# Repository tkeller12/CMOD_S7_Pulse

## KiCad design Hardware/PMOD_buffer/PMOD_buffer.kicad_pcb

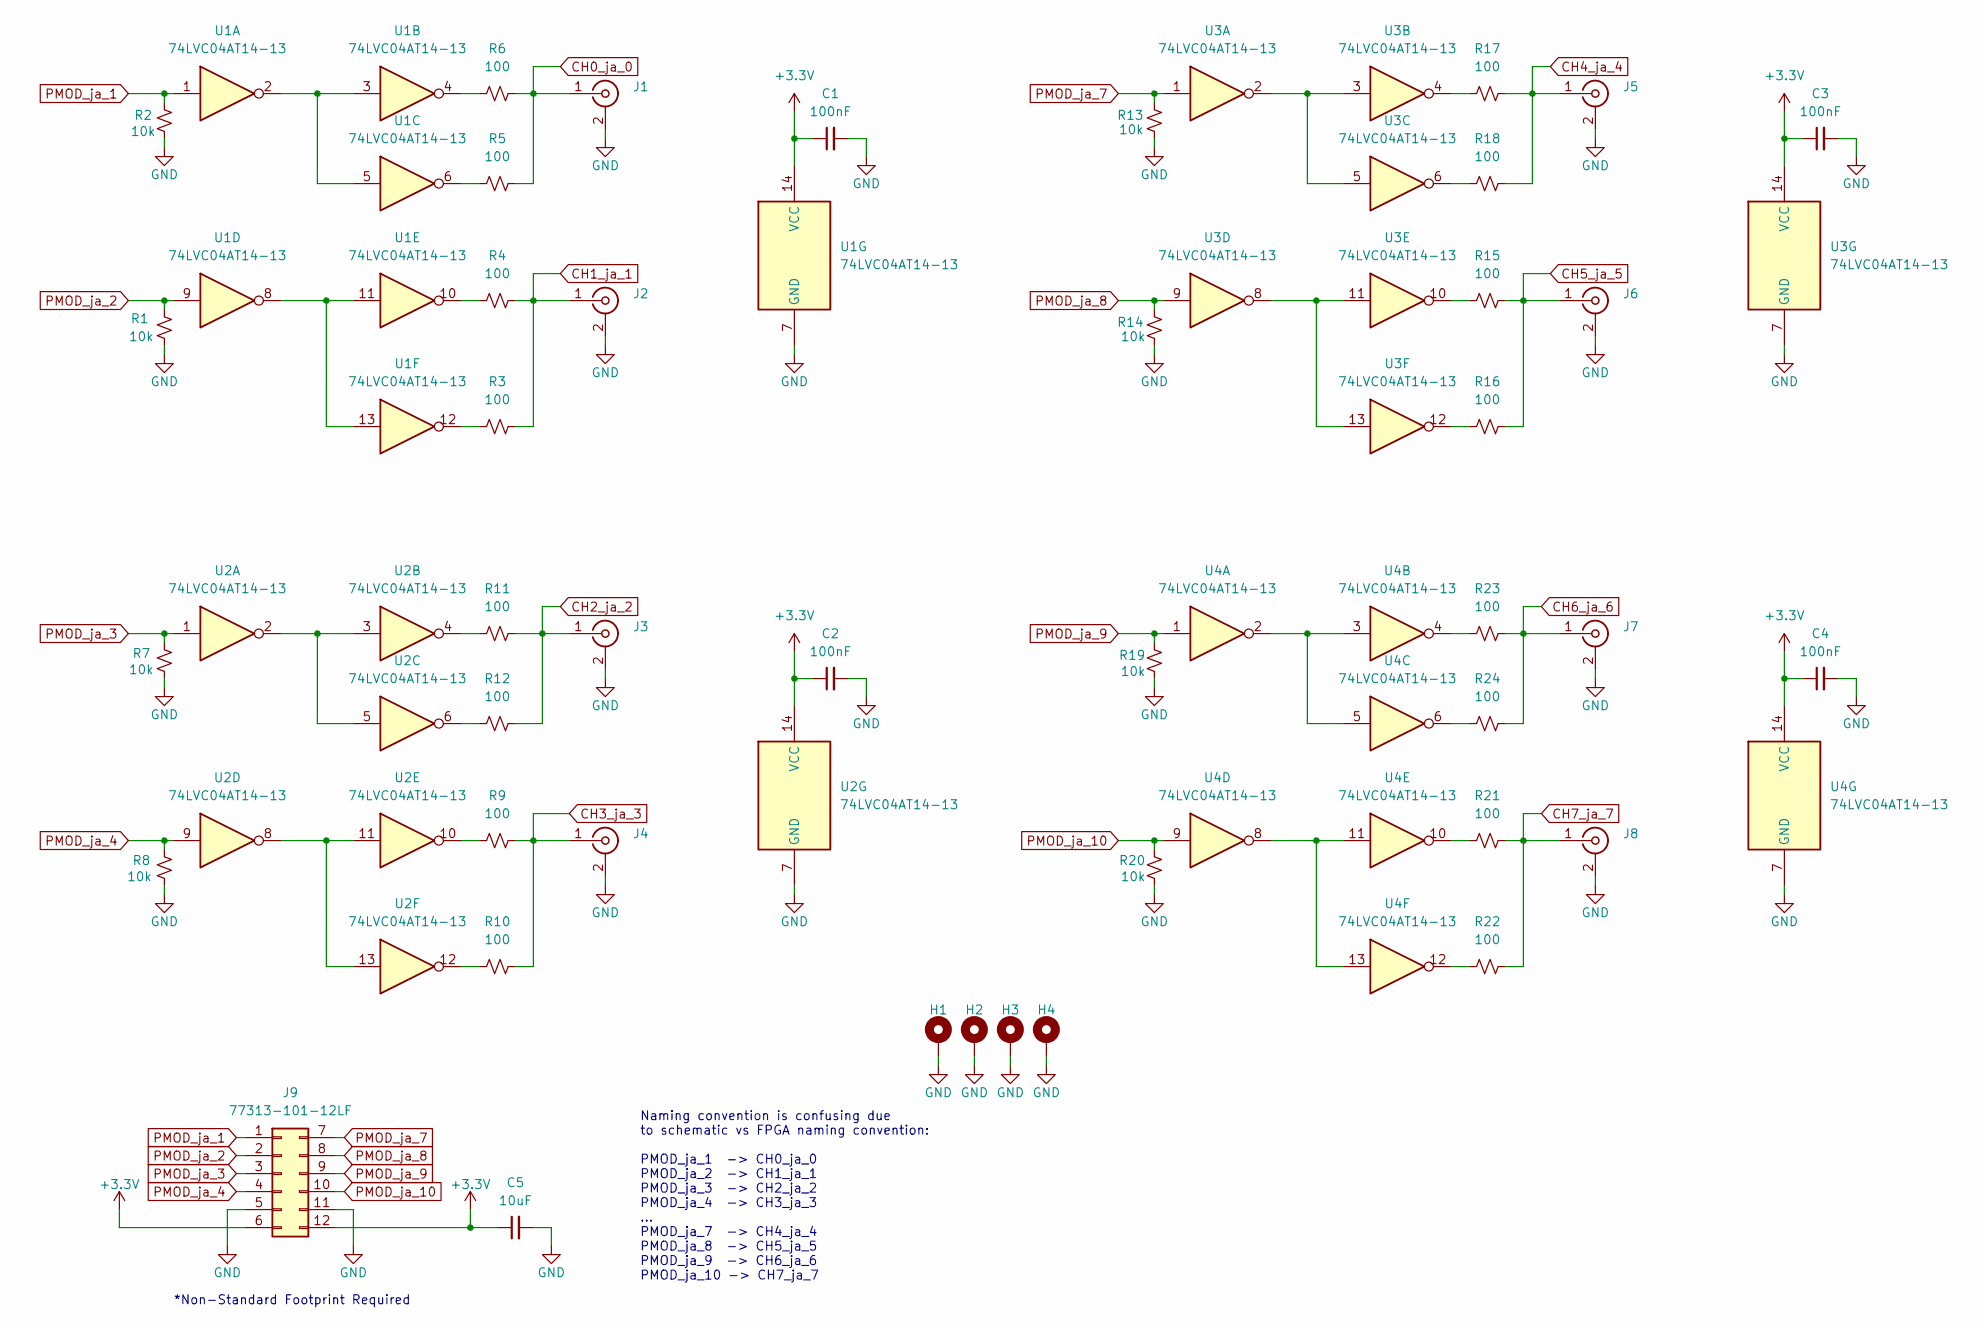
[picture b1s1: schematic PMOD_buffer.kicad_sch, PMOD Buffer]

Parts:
C1, C2, C3, C4: 100nF; C_0805_2012Metric; MPN KGM21NR71H104KT; Digikey 478-KGM21NR71H104KTCT-ND
C5: 10uF; C_0805_2012Metric; MPN CL21A106KOQNNNG; Digikey 1276-6455-1-ND
H1, H2, H3, H4: MountingHole_Pad; 4-40_Hole_Pad
J1, J2, J3, J4, J5, J6, J7, J8: RF2-152-T-00-50-G-HDW; SMA_Amphenol_132291_Vertical; MPN RF2-152-T-00-50-G-HDW; Digikey 2057-RF2-152-T-00-50-G-HDW-ND
J9: 77313-101-12LF; PMOD_PinHeader_2x06_P2.54mm_Vertical; MPN 77313-101-12LF; Digikey 609-5695-ND
R1, R2, R7, R8, R13, R14, R19, R20: 10k; R_0805_2012Metric; MPN CRCW080510K0FKEAC; Digikey 541-3976-1-ND
R3, R4, R5, R6, R9, R10, R11, R12, R15, R16, R17, R18, R21, R22, R23, R24: 100; R_0805_2012Metric; MPN RMCF0805FT100R; Digikey RMCF0805FT100RCT-ND
U1, U2, U3, U4: 74LVC04AT14-13; TSSOP-14_4.4x5mm_P0.65mm; MPN 74LVC04AT14-13; Digikey 31-74LVC04AT14-13CT-ND

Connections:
+3.3V: C1.1, C2.1, C3.1, C4.1, C5.1, J9.6, J9.12, U1.14 (VCC), U2.14 (VCC), U3.14 (VCC), U4.14 (VCC)
CH0_ja_0: J1.1 (In), R5.2, R6.2
CH1_ja_1: J2.1 (In), R3.2, R4.2
CH2_ja_2: J3.1 (In), R11.2, R12.2
CH3_ja_3: J4.1 (In), R9.2, R10.2
CH4_ja_4: J5.1 (In), R17.2, R18.2
CH5_ja_5: J6.1 (In), R15.2, R16.2
CH6_ja_6: J7.1 (In), R23.2, R24.2
CH7_ja_7: J8.1 (In), R21.2, R22.2
GND: C1.2, C2.2, C3.2, C4.2, C5.2, H1.1, H2.1, H3.1, H4.1, J1.2 (Ext), J2.2 (Ext), J3.2 (Ext), J4.2 (Ext), J5.2 (Ext), J6.2 (Ext), J7.2 (Ext), J8.2 (Ext), J9.5, J9.11, R1.2, R2.2, R7.2, R8.2, R13.2, R14.2, R19.2, R20.2, U1.7 (GND), U2.7 (GND), U3.7 (GND), U4.7 (GND)
unnamed: R3.1, U1.12
unnamed: R4.1, U1.10
unnamed: R5.1, U1.6
unnamed: R6.1, U1.4
unnamed: R9.1, U2.10
unnamed: R10.1, U2.12
unnamed: R11.1, U2.4
unnamed: R12.1, U2.6
unnamed: R15.1, U3.10
unnamed: R16.1, U3.12
unnamed: R17.1, U3.4
unnamed: R18.1, U3.6
unnamed: R21.1, U4.10
unnamed: R22.1, U4.12
unnamed: R23.1, U4.4
unnamed: R24.1, U4.6
unnamed: U1.2, U1.3, U1.5
unnamed: U1.8, U1.11, U1.13
unnamed: U2.2, U2.3, U2.5
unnamed: U2.8, U2.11, U2.13
unnamed: U3.2, U3.3, U3.5
unnamed: U3.8, U3.11, U3.13
unnamed: U4.2, U4.3, U4.5
unnamed: U4.8, U4.11, U4.13
PMOD_ja_1: J9.1, R2.1, U1.1
PMOD_ja_2: J9.2, R1.1, U1.9
PMOD_ja_3: J9.3, R7.1, U2.1
PMOD_ja_4: J9.4, R8.1, U2.9
PMOD_ja_7: J9.7, R13.1, U3.1
PMOD_ja_8: J9.8, R14.1, U3.9
PMOD_ja_9: J9.9, R19.1, U4.1
PMOD_ja_10: J9.10, R20.1, U4.9

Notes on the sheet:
*Non-Standard Footprint Required
Naming convention is confusing due to schematic vs FPGA naming convention: PMOD_ja_1 -> CH0_ja_0 PMOD_ja_2 -> CH1_ja_1 PMOD_ja_3 -> CH2_ja_2 PMOD_ja_4 -> CH3_ja_3 ... PMOD_ja_7 -> CH4_ja_4 PMOD_ja_8 -> CH5_ja_5 PMOD_ja_9 -> CH6_ja_6 PMOD_ja_10 -> CH7_ja_7

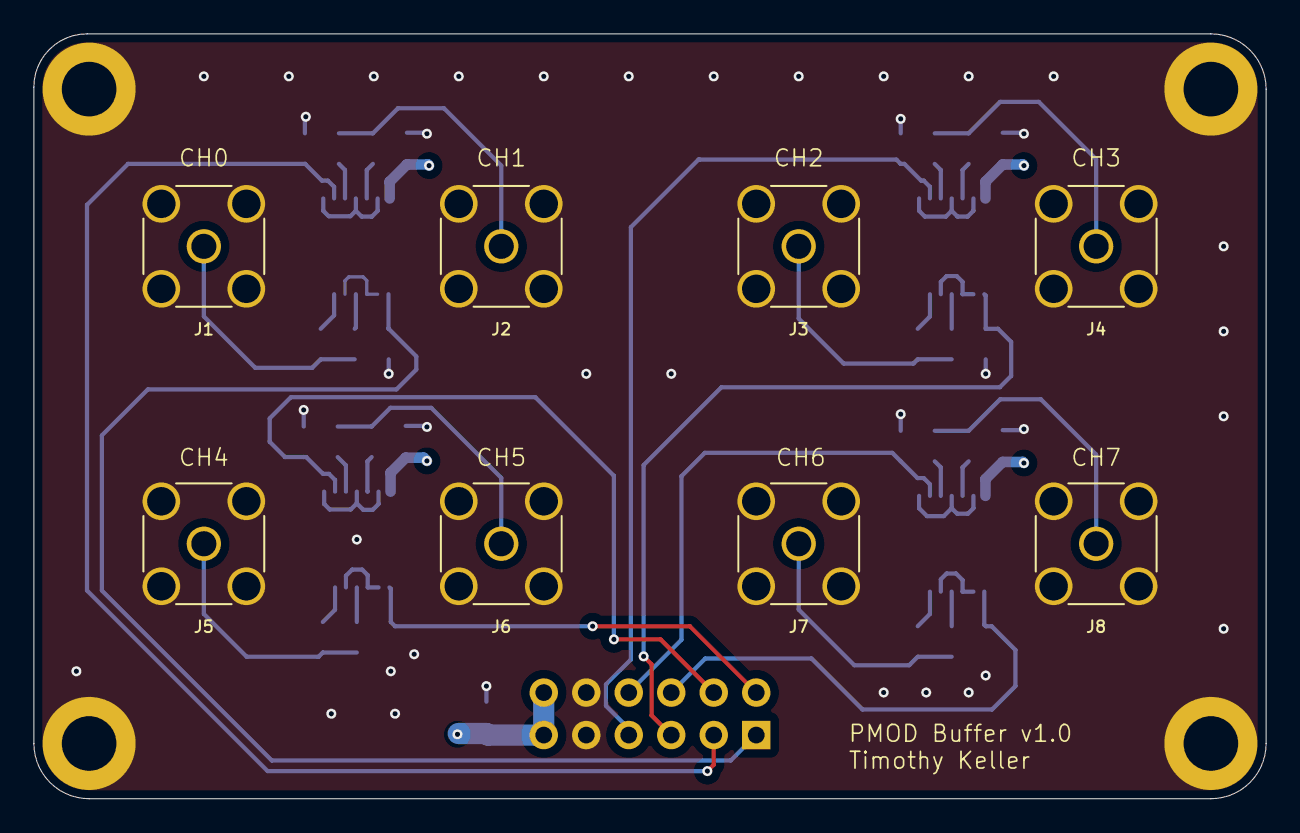
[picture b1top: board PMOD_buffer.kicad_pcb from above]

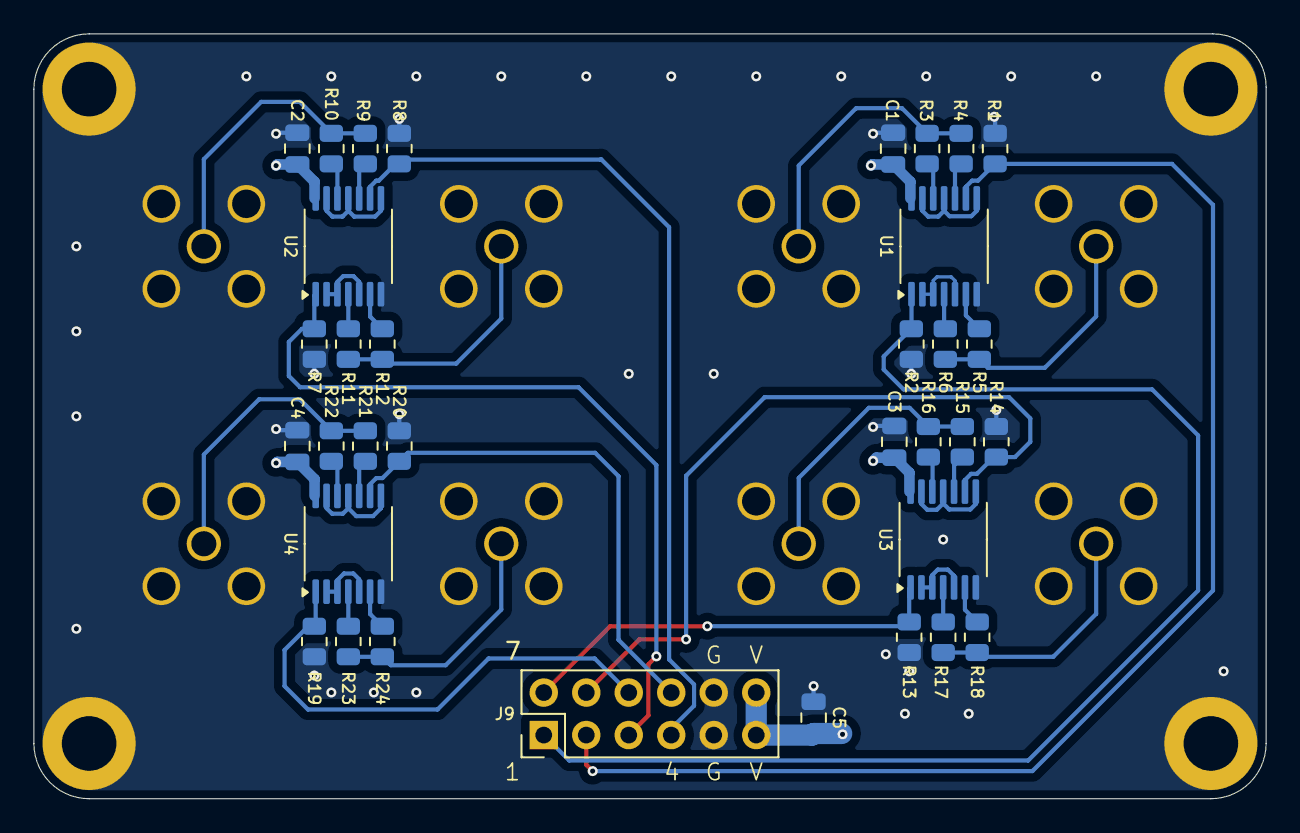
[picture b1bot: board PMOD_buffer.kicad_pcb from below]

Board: 4 copper layers, 73.7 x 45.7 mm, 46 parts (34 on the bottom side), 42 nets.

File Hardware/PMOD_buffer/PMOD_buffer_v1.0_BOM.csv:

"Reference","Value","Datasheet","Footprint","Qty","DNP","Digikey","MPN","Manufacturer","Description"
"C1,C2,C3,C4","100nF","~","Capacitor_SMD:C_0805_2012Metric","4","","478-KGM21NR71H104KTCT-ND","KGM21NR71H104KT","KYOCERA AVX","CAP CER 0.1UF 50V X7R 0805"
"C5","10uF","~","Capacitor_SMD:C_0805_2012Metric","1","","1276-6455-1-ND","CL21A106KOQNNNG","Samsung Electro-Mechanics","CAP CER 10UF 16V X5R 0805"
"J1,J2,J3,J4,J5,J6,J7,J8","RF2-152-T-00-50-G-HDW","RF2-152-T-00-50-G-HDW","Connector_Coaxial:SMA_Amphenol_132291_Vertical","8","","2057-RF2-152-T-00-50-G-HDW-ND","RF2-152-T-00-50-G-HDW","Adam Tech","SMA JACK STR PCB 50OHM 18GHZ BRS"
"J9","77313-101-12LF","~","_tim-Headers:PMOD_PinHeader_2x06_P2.54mm_Vertical","1","","609-5695-ND","77313-101-12LF","Amphenol ICC (FCI)","CONN HEADER VERT 12POS 2.54MM"
"R1,R2,R7,R8,R13,R14,R19,R20","10k","~","Resistor_SMD:R_0805_2012Metric","8","","541-3976-1-ND","CRCW080510K0FKEAC","Vishay Dale","RES 10K OHM 1% 1/8W 0805"
"R3,R4,R5,R6,R9,R10,R11,R12,R15,R16,R17,R18,R21,R22,R23,R24","100","~","Resistor_SMD:R_0805_2012Metric","16","","RMCF0805FT100RCT-ND","RMCF0805FT100R","Stackpole Electronics Inc","RES 100 OHM 1% 1/8W 0805"
"U1,U2,U3,U4","74LVC04AT14-13","http://www.ti.com/lit/gpn/sn74LS04","Package_SO:TSSOP-14_4.4x5mm_P0.65mm","4","","31-74LVC04AT14-13CT-ND","74LVC04AT14-13","Diodes Incorporated","IC INVERTER 6CH 6-INP 14TSSOP"

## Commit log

2024-11-26 Creating Vivado project
2024-11-26 Creating Schematic
2024-11-27 Routing Board
2024-11-28 Adding clocks
2024-12-03 Testing Shift Register
2024-12-04 Removing unnecessary modules
2024-12-04 backups
2024-12-14 Adding vivado project
2024-12-14 WIP Updating pulse programmer verilog code
2024-12-14 Testing pulse programmer core
2024-12-15 Updating pulse programmer core test
2024-12-15 Updating pulse programmer core
2024-12-15 Updating pulse programmer verilog code
2024-12-15 Pulse Programmer working
    WIP addr 0 does not work properly
2024-12-15 Updating python script for writing to pulse programmer
2024-12-15 minor change to python script
2024-12-16 testing dds core
2024-12-16 Minor changes
2024-12-18 Adding gitignore for vim files
2024-12-18 Adding simple blink example
2024-12-18 Using Standard 2-port RAM and assign statements
2024-12-19 Updating RAM
2024-12-19 Implemented wait op code
2024-12-19 Adding GOTO op code
2024-12-20 Implementing Long delay op code
2024-12-23 Adding memory config
2024-12-24 Adding start and stop commands
2024-12-27 Adding simulation to test
2024-12-27 Updating Clocking wizard
2024-12-30 Changing back to 250 MHz clock
2025-07-06 Updating PMOD Buffer BOM
2025-07-07 adding BOM for buffer board
2025-07-07 Generating Gerbers for Buffer
2025-07-11 Adding fab and assem files
2025-07-18 Adding python scripts to generate pulse sequence
2025-07-18 Adding new pulse generator script
2025-07-19 Updates to pulse train script
2025-07-19 Working example for pulse programming sequence
2025-07-19 implementation runs, but can't upload to board
2025-07-19 Fixing issue with severe clock violations, now using 125 MHz clock
2025-07-19 Fixing fpga configuration, new memory file
2025-07-19 Moving examples to new directory
2025-07-19 Creating new python package for pulse programmer
2025-07-19 Updating python package, adding config support
2025-07-19 Created working example
2025-07-19 Cleaning up code
2025-07-19 Adding plot module
2025-07-19 Updating plot function
2025-07-20 Autodetecting serial port
2025-07-20 Fixing issue with plot, adding new troubleshooting script
2025-07-20 Updating documentation with photos
2025-07-20 Cleaning up example script
2026-03-14 Changing clock frequency back to 250 MHz
2026-03-14 Updating documentation for pulse programmer op codes
2026-03-14 updating python scripts for testing, changing resolution to 4ns
2026-03-14 Updating Verilog for 250 MHz clock, fixed bug with address 0
2026-03-14 Adding JUMP op code to pulse programmer
2026-03-15 Adding external clock wizard
2026-03-15 Changing clock to 125 MHz
2026-03-15 Updating documentation, adding table for instructions
2026-03-15 Working on fixing bug with jump
2026-03-16 creating test bench for top module
2026-03-16 Troubleshooting issue with BRAM latency
2026-03-17 Updating pulse programmer core to remove address increment bug
2026-03-17 Adding new memory configuration
2026-03-17 minor change. Added reset for clock
2026-03-17 Auto stash before merge of "develop" and "feature-EXT_10MHz_CLK"
2026-03-17 Updating FPGA frequency to 250 MHz
2026-03-18 Updating documentation
2026-03-21 testing clock frequencies
2026-03-21 Adding lexer
2026-03-21 Starting parser
2026-03-21 Updates to lexer and parser
2026-03-22 Starting to implement AST
2026-03-22 Adding Pulse programmer documentation, support for comments
2026-03-23 Working on edges to states function
2026-03-23 Adding generate_instructions function
2026-03-23 fixing minor bug
2026-03-23 adding plot for states
2026-03-23 Changing config format
2026-03-23 Fixing connectivity bug and cleaning up code
2026-03-23 Moving inverting bits to states
2026-03-24 Adding checks for duty cycle limit and max pulse length limit
2026-03-24 Fixing issue with remove_redundant_edges function
2026-03-24 Adding function to write instructions to file
2026-03-25 Adding new simulation with memory load from file
2026-03-25 Fixing glitch with output during JUMP instruction
2026-03-25 removing comment
2026-03-25 Adding HALT Command
2026-03-26 wip testing LOOP_START and LOOP_STOP
2026-03-26 Simulation for loop works
2026-03-26 Loops only work with no-op around start and stop
2026-03-27 Loops only work with no-op before halt
2026-03-27 Seems like loops are working
2026-03-27 creating new memory configuration
2026-03-28 Fixing bug with loops and executing first address twice
2026-03-28 Fixing bug with executing first address twice
    start pulse sends core to address 2
2026-03-29 Working on fixing bug with different pulse length in first loop iteration
2026-03-29 Improved timing violations
2026-03-29 Fixed bug with address for LOOP_START command
2026-04-04 Updating UART baud rate to 1M
2026-04-04 Minor update to documentation
2026-04-04 Testing the serializer
2026-04-05 RGB LED now disabled (off) on board
